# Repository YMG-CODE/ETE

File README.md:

# ETE_Ergo the End
ETE_Ergo The End keyboard, a split keyboard with  column staggered 62 keys and LED indicators.

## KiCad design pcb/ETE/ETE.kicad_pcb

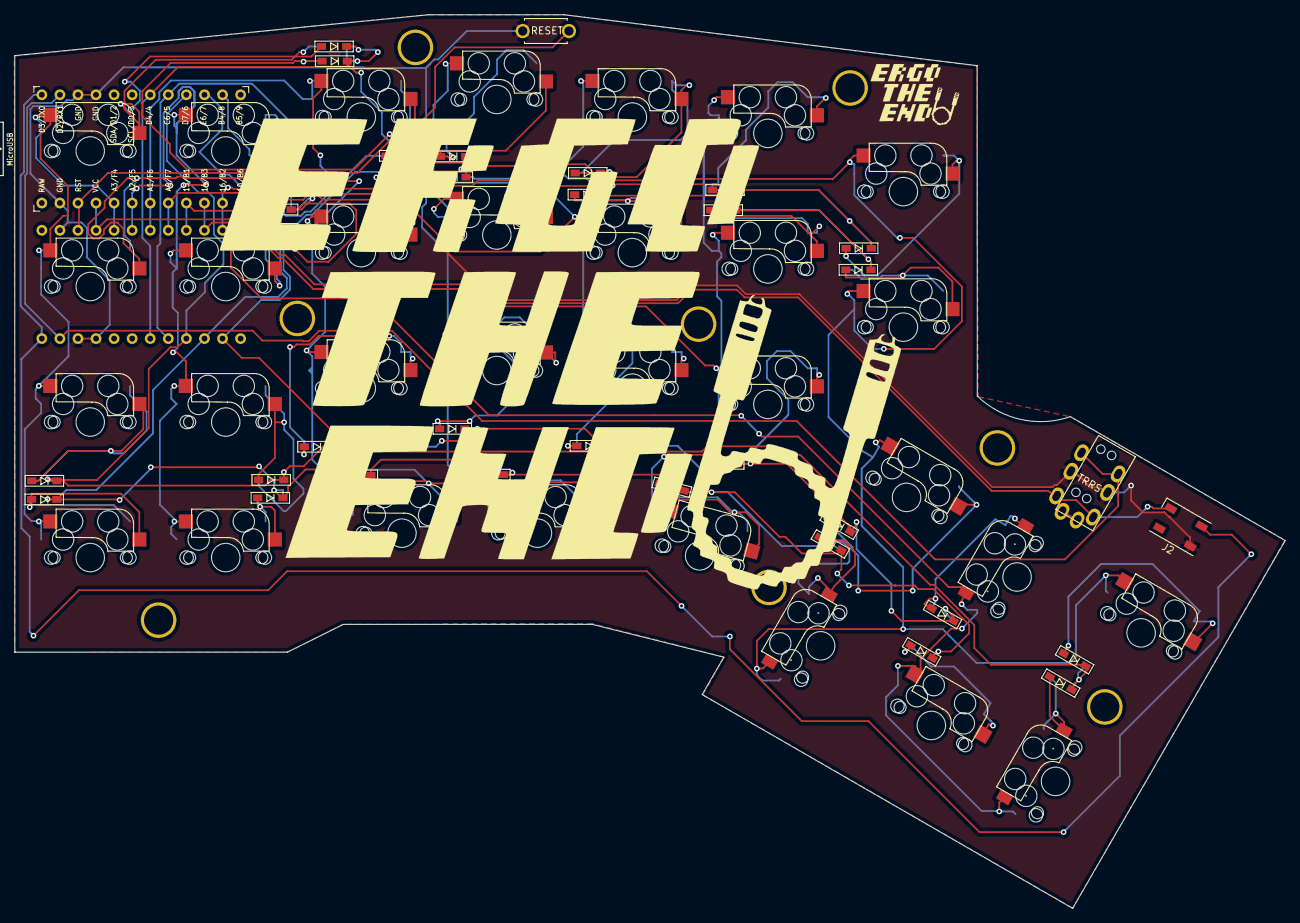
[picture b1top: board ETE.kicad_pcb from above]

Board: 2 copper layers, 178.6 x 125.6 mm, 76 parts (1 on the bottom side), 49 nets.

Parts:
 : LOGO; ETE_logo4
D1, D2, D3, D4, D5, D6, D7, D15, D16, D17, D18, D19, D20, D21, D29, D30, D31, D32, D33, D34, D35, D36, D45, D46, D47, D48, D49, D50, D201, D202, D203: DIODE; D3_SMD_R
J1: MJ-4PP-9
J2: LED; LED_WS2812B-PLCC4
RSW1: SW_Push; ResetSW
Ref**: Val**; HOLE
Ref**#2, Ref**#3, Ref**#4, Ref**#5, Ref**#6, Ref**#7, Ref**#8: Val**; HOLE
SW1, SW2, SW3, SW4, SW5, SW6, SW7, SW15, SW16, SW17, SW18, SW19, SW20, SW21, SW29, SW30, SW31, SW32, SW33, SW34, SW35, SW36, SW45, SW46, SW47, SW48, SW49, SW50: SW_Push; CherryMX_Hotswap_1u
SW201, SW202, SW203: SW_Push; CherryMX_Hotswap_1.5u
U1, U2: ProMicro_r; ProMicro_v3_con

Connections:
GND: J1.C, J2.1, RSW1.2, U1.3, U1.4, U1.23, U2.3, U2.4, U2.23
LED: J2.2, U1.1, U2.1
unnamed: D1.1, SW1.2
unnamed: D2.1, SW2.2
unnamed: D3.1, SW3.2
unnamed: D4.1, SW4.2
unnamed: D5.1, SW5.2
unnamed: D6.1, SW6.2
unnamed: D7.1, SW7.2
unnamed: D15.1, SW15.2
unnamed: D16.1, SW16.2
unnamed: D17.1, SW17.2
unnamed: D18.1, SW18.2
unnamed: D19.1, SW19.2
unnamed: D20.1, SW20.2
unnamed: D21.1, SW21.2
unnamed: D29.1, SW29.2
unnamed: D30.1, SW30.2
unnamed: D31.1, SW31.2
unnamed: D32.1, SW32.2
unnamed: D33.1, SW33.2
unnamed: D34.1, SW34.2
unnamed: D35.1, SW35.2
unnamed: D36.1, SW36.2
unnamed: D45.1, SW45.2
unnamed: D46.1, SW46.2
unnamed: D47.1, SW47.2
unnamed: D48.1, SW48.2
unnamed: D49.1, SW49.2
unnamed: D50.1, SW50.2
unnamed: D201.1, SW201.2
unnamed: D202.1, SW202.2
unnamed: D203.1, SW203.2
VCC: J1.D, J2.3, U1.21, U2.21
col0: SW1.1, SW15.1, SW29.1, SW45.1, U1.20, U2.20
col1: SW2.1, SW16.1, SW30.1, SW46.1, U1.19, U2.19
col2: SW3.1, SW17.1, SW31.1, SW47.1, U1.18, U2.18
col3: SW4.1, SW18.1, SW32.1, SW48.1, U1.17, U2.17
col4: SW5.1, SW19.1, SW33.1, U1.16, U2.16
col5: SW6.1, SW20.1, SW34.1, SW49.1, U1.15, U2.15
col6: SW7.1, SW21.1, SW35.1, SW36.1, SW201.1, U1.14, U2.14
col7: SW50.1, SW202.1, SW203.1, U1.13, U2.13
data: J1.B, U1.2, U2.2
reset: RSW1.1, U1.22, U2.22
row0: D1.2, D2.2, D3.2, D4.2, D5.2, D6.2, D7.2, U1.7, U2.7
row1: D15.2, D16.2, D17.2, D18.2, D19.2, D20.2, D21.2, U1.8, U2.8
row2: D29.2, D30.2, D31.2, D32.2, D33.2, D34.2, D35.2, D202.2, U1.9, U2.9
row3: D45.2, D46.2, D47.2, D48.2, D49.2, D50.2, D201.2, U1.10, U2.10
row4: D36.2, D203.2, U1.11, U2.11

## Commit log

2024-01-23 Create drivers
2024-01-23 Create test
2025-05-30 Create hex
